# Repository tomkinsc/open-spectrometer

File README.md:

The OpenSpectrometer project is a collaborative effort to create freely-available mechanical designs, electronic plans, and software for a USB spectrophotometer. The end goal is an instrument that is inexpensive to build, easy to use, simple to modify, and as accurate and precise as a commercial off-the-shelf unit.

The OpenSpectrometer will integrate commercially-available electronic and optics parts with custom printed circuit boards (PCBs) and an inexpensive a wooden enclosure.

Beyond hardware, the project will develop embedded firmware, and desktop user software, and an online community-driven spectral database.

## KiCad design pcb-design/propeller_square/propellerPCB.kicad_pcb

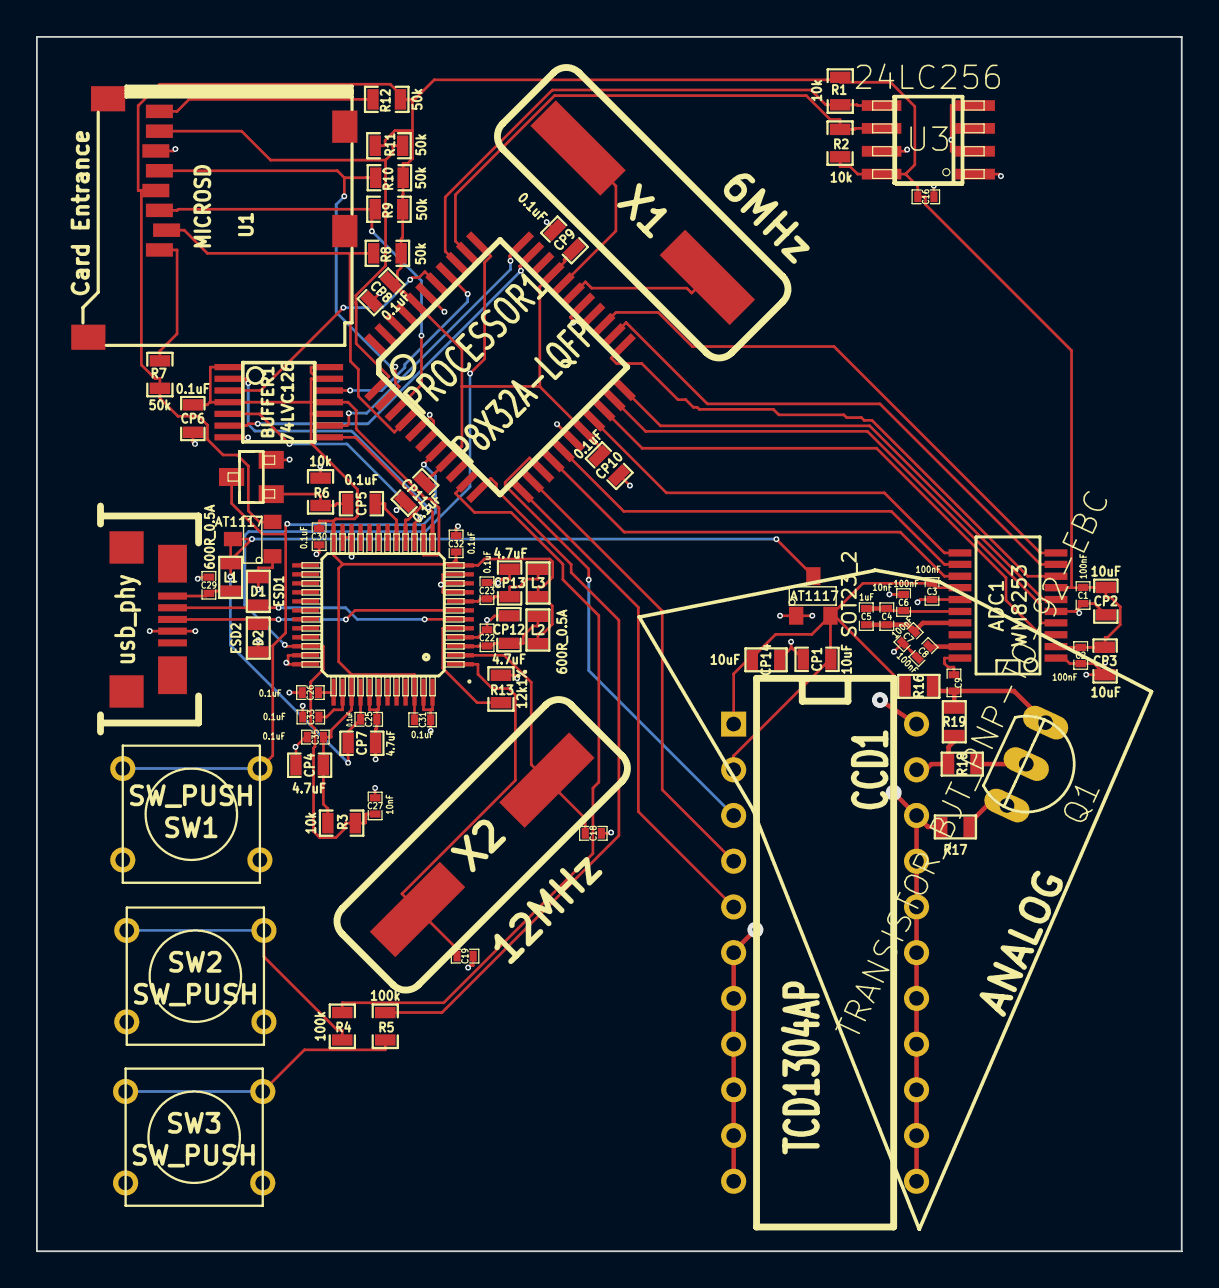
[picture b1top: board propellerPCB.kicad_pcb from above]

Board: 4 copper layers, 63.6 x 67.5 mm, 76 parts (0 on the bottom side), 61 nets.

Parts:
ADC1: WM8253; SSOP20
BUFFER1: 74LVC126; TSSOP14_0.65mmPitch_4.4mmWide_PW
C1, C2, C3, C6, C7, C8: 100nF; SM0402_c
C4, C27, C29: 10nF; SM0402_c
C5, C16: 1uF; SM0402_c
C9: 200pF; SM0402_c
C18, C19: 27pF; SM0402_c
C22, C23, C25, C26, C30, C31, C32, C33, C35: 0.1uF; SM0402_c
CCD1: TCD1304AP; DIP-22__400
CP1, CP2, CP3, CP14: 10uF; SM0603_Capa
CP4, CP7, CP12, CP13: 4.7uF; SM0603_Capa
CP5, CP6, CP8, CP9, CP10, CP11: 0.1uF; SM0603_Capa
D1: ESD1; SM0603
D2: ESD2; SM0603
FTDI1: FT232HL; dp_devices-LQFP48
L1, L2, L3: 600R_0.5A; SM0603
PROCESSOR1: P8X32A-LQFP; TQFP44
Q1: TRANSISTOR_BJT_PNP-TO-92-EBC; dp_devices-TO-92
R1, R2, R3, R6: 10k; SM0603_Resistor
R4, R5: 100k; SM0603_Resistor
R7, R8, R9, R10, R11, R12: 50k; SM0603_Resistor
R13: 12k1%; SM0603_Resistor
R16: 2200; SM0603
R17, R18: 150; SM0603
R19: 0; SM0603
SOT23_1, SOT23_2: AT1117; SOT23
SW1, SW2, SW3: SW_PUSH; SW_PUSH_SMALL
T1: TRANSISTOR_BJT_NPN-SOT-23-BEC; dp_devices-SOT-23
U1: MICROSD; Memory_Card_microSD_3M_290805
U3: 24LC256; dp_devices-SOIC-8
USB_HOLES1: usb_phy; MICROUSB-B-ZX62-B-5PA
X1: 6MHz; CRYSTAL-HC49-US
X2: 12MHz; CRYSTAL-HC49-US

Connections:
/ADC_INPUT: ADC1.20, C9.1
/ADC_p16: ADC1.16, C4.2, C5.2, C6.2
/ADC_p17: ADC1.17, C4.1, C5.1, C7.1
/AVDD: ADC1.14, C3.1, CCD1.1, CCD1.2, CP1.1, CP14.1, R16.1, SOT23_2.2
/CCD_MCLK: CCD1.4, PROCESSOR1.13
/CTS: BUFFER1.9, PROCESSOR1.33
/DM: D1.2, FTDI1.6, USB_HOLES1.2
/DP: D2.2, FTDI1.7, USB_HOLES1.3
/DTR: CP5.1, FTDI1.17
/DVDD1: ADC1.2, ADC1.7, C1.1, C2.1, C16.1, CP2.1, CP3.1, CP8.1, CP9.1, CP10.1, CP11.1, PROCESSOR1.8, PROCESSOR1.18, PROCESSOR1.30, PROCESSOR1.40, R1.2, R2.2, R7.1, R8.1, R9.1, R10.1, R11.1, R12.1, SOT23_1.2, U1.4, U3.8
/FTDI_CTS: BUFFER1.8, FTDI1.16
/FTDI_REF: FTDI1.5, R13.2
/FTDI_RTS: BUFFER1.5, FTDI1.15
/FTDI_RXD: BUFFER1.11, FTDI1.14
/FTDI_TXD: BUFFER1.2, FTDI1.13
/ICG: CCD1.3, PROCESSOR1.14
/MCLK: ADC1.4, PROCESSOR1.21
/OP_0: ADC1.10, PROCESSOR1.25
/OP_1: ADC1.11, PROCESSOR1.19
/OP_2: ADC1.12, PROCESSOR1.16
/OP_3: ADC1.13, PROCESSOR1.15
/OS/VOUT: CCD1.21, R18.1, R19.1
/OSCI2: C19.2, FTDI1.1, X2.1
/OSCO2: C18.2, FTDI1.2, X2.2
/PROP_RX: BUFFER1.3, PROCESSOR1.38
/PROP_TX: BUFFER1.12, PROCESSOR1.37
/RESN: PROCESSOR1.7, SW1.2, T1.3
/RES_GATE: CP5.2, R6.2, T1.1
/RTS: BUFFER1.6, PROCESSOR1.32
/SCK: ADC1.9, PROCESSOR1.24
/SCL: PROCESSOR1.35, R2.1, U3.6
/SDA: PROCESSOR1.36, R1.1, U3.5
/SDI: ADC1.8, PROCESSOR1.23
/SEN: ADC1.6, PROCESSOR1.22
/SH: CCD1.5, PROCESSOR1.12
/SW2: PROCESSOR1.10, R4.1
/SW3: PROCESSOR1.11, R5.1
/USB_5V: C29.1, L1.1, USB_HOLES1.1
/USB_RESET: C27.2, FTDI1.34, PROCESSOR1.34, R3.2
/VBUS: C25.2, CP7.1, FTDI1.40, L1.2, SOT23_1.3, SOT23_2.3
/VCC3.3V: BUFFER1.1, BUFFER1.4, BUFFER1.10, BUFFER1.13, BUFFER1.14, C30.1, C31.1, C32.1, C35.1, CP4.1, CP6.1, FTDI1.12, FTDI1.24, FTDI1.39, FTDI1.46, L2.2, L3.2, R3.1
/VCORE: C33.1, FTDI1.38
/VPHY: C22.1, CP12.1, FTDI1.3, L2.1
/VPLL: C23.1, CP13.1, FTDI1.8, L3.1
/VSMP: ADC1.3, PROCESSOR1.20
/X0_Prop: PROCESSOR1.29, X1.1
/XI_Prop: PROCESSOR1.28, X1.2
/uSD_CLK: PROCESSOR1.2, R10.2, U1.5
/uSD_CS: PROCESSOR1.4, R8.2, U1.2
/uSD_DI: PROCESSOR1.3, R9.2, U1.3
/uSD_DO: PROCESSOR1.1, R11.2, U1.7
/uSD_NC1: R7.2, U1.1
/uSD_NC2: R12.2, U1.8
AGND: ADC1.1, ADC1.5, ADC1.15, BUFFER1.7, C1.2, C2.2, C3.2, C6.1, C7.2, C8.2, C16.2, C18.1, C19.1, C22.2, C23.2, C25.1, C26.1, C27.1, C29.2, C30.2, C31.2, C32.2, C33.2, C35.2, CCD1.6, CCD1.7, CCD1.8, CCD1.9, CCD1.10, CCD1.11, CCD1.12, CCD1.13, CCD1.14, CCD1.15, CCD1.16, CCD1.17, CCD1.18, CCD1.19, CCD1.20, CCD1.22, CP1.2, CP2.2, CP3.2, CP4.2, CP6.2, CP7.2, CP8.2, CP9.2, CP10.2, CP11.2, CP12.2, CP13.2, CP14.2, D1.1, D2.1, FTDI1.4, FTDI1.9, FTDI1.10, FTDI1.11, FTDI1.22, FTDI1.23, FTDI1.35, FTDI1.36, FTDI1.41, FTDI1.42, FTDI1.47, FTDI1.48, PROCESSOR1.5, PROCESSOR1.6, PROCESSOR1.17, PROCESSOR1.27, PROCESSOR1.39, R6.1, R13.1, R17.1, SOT23_1.1, SOT23_2.1, SW1.1, SW2.2, SW3.2, T1.2, U1.6, U3.1, U3.2, U3.3, U3.4, U3.7, USB_HOLES1.4
unnamed: C9.2, Q1.1, R16.2, R19.2
unnamed: Q1.2, R18.2
unnamed: Q1.3, R17.2
unnamed: C26.2, FTDI1.37
unnamed: R4.2, SW2.1
unnamed: R5.2, SW3.1
unnamed: ADC1.19, C8.1

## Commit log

2011-10-10 initial commit of README.md and rough case design (designed for 5.5mm tri-ply)
2011-10-18 established directory structure to organize project files
2011-10-18 added readme files
2011-10-23 first commit of tilt_mount.dwg
2011-11-15 First pass at a working CCD, SH (exposure time GPIO) period widens when I allow the ISR to get pixels... this needs fixed so the ISR is on a different PWM line that can just be totally turned off/on
2011-12-14 first go try at a block diagram of the overall system
2012-01-02 changed comments, added comments
2012-01-02 changed more comments
2013-01-25 parser for biowave_II added, in phPython.py you can averaging datasets, fitting a curve to them and use that to searching for peaks (lambda max), the fit line and original data are plotted and the po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
2013-01-25 changed openSpectrometerGUI to openSpectrometer
2013-01-25 changed filename from openSpectrometerGUI to openSpectrometer
2013-07-30 added propeller code to get data from the TCD1304ap ccd
2014-01-30 Added comments, tested with oscilloscope, removed need for sense pin (you can use waitpeq directly on a counter compare output pin), added restarting the CCD at the end of one loop to keep clocking f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
2014-01-30 forgot to remove all the sense pin stuff last commit, removed it now.
2014-02-03 changed pins because I connected the WM8253 ADC
2014-06-04 added kicad project files, and some of the library module files. unproven half-autorouted but seems pretty good, 4-layer board 2.51x2.66 inches (63.70x67.56 mm), done in kicad
2014-06-04 added pic of schematic
